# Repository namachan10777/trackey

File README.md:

# Trackey

A splited keyboard that has trackball.

# License
MIT License.

Copyright (c) 2018 Nakano Masaki

## Exception
 * ./pcb/lib/trackey.pretty/MX_ALPS_KH_u1.00.kicad_mod
 * ./pcb/lib/trackey.pretty/D_SOD-123.kicad_mod
 * ./pcb/lib/trackey.pretty/LED_D3.0mm.kicad_mod
 * ./pcb/lib/trackey.pretty/R_Axial.kicad_mod
 * ./pcb/lib/trackey.pretty/SW_Tactile_SPST_Angled.kicad_mod
These footprint's original author is KiCAD.
These are distributed under CC-BY-SA 4.0.

# Third party
## helix
### point of use
 * Key footprint (./pcb/lib/trackey.pretty/MX_ALPS_KH_u1.00.kicad_mod) (modified)
 * Audio Jack footprint (./pcb/lib/trackey.pretty/MJ-4PP-9_rev2.kicad_mod)
### LICENSE
>Copyright (c) 2018 MakotoKurauchi
>
>Permission is hereby granted, free of charge, to any person obtaining a copy
>of this software and associated documentation files (the "Software"), to deal
>in the Software without restriction, including without limitation the rights
>to use, copy, modify, merge, publish, distribute, sublicense, and/or sell
>copies of the Software, and to permit persons to whom the Software is
>furnished to do so, subject to the following conditions:
>
>The above copyright notice and this permission notice shall be included in all
>copies or substantial portions of the Software.
>
>THE SOFTWARE IS PROVIDED "AS IS", WITHOUT WARRANTY OF ANY KIND, EXPRESS OR
>IMPLIED, INCLUDING BUT NOT LIMITED TO THE WARRANTIES OF MERCHANTABILITY,
>FITNESS FOR A PARTICULAR PURPOSE AND NONINFRINGEMENT. IN NO EVENT SHALL THE
>AUTHORS OR COPYRIGHT HOLDERS BE LIABLE FOR ANY CLAIM, DAMAGES OR OTHER
>LIABILITY, WHETHER IN AN ACTION OF CONTRACT, TORT OR OTHERWISE, ARISING FROM,
>OUT OF OR IN CONNECTION WITH THE SOFTWARE OR THE USE OR OTHER DEALINGS IN THE
>SOFTWARE.

## KiCAD Library
### LICENSE
CC-BY-SA 4.0
Copyright (c) KiCAD

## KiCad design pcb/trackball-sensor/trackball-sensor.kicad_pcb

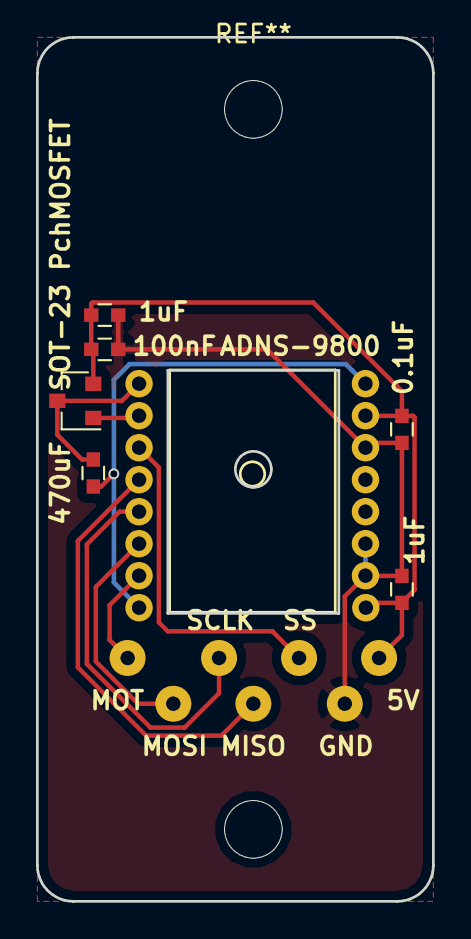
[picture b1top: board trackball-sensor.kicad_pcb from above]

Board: 2 copper layers, 22.0 x 48.0 mm, 14 parts (0 on the bottom side), 10 nets.

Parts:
C1, C4: 1uF; C_0603
C2: 0.1uF; C_0603
C3: 470pF; C_0603
C5: 100nF; C_0603
J1, J2, J3, J4, J5, J6, J7: Conn_01x01; SolderWirePad_single_0-8mmDrill
Q1: Q_PMOS_GDS; SOT-23
U1: ADNS-9800

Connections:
+5V: C1.1, C2.1, C4.2, C5.2, J1.1, Q1.2, U1.9, U1.15
/MISO: J4.1, U1.4
/MOSI: J3.1, U1.6
/MOTION: J6.1, U1.7
/SCLK: J2.1, U1.5
/SS: J5.1, U1.3
GND: C1.2, C2.2, C4.1, C5.1, J7.1, U1.10, U1.11, U1.14
unnamed: C3.1, Q1.3, U1.1
unnamed: C3.2, U1.8, U1.16
unnamed: Q1.1, U1.2

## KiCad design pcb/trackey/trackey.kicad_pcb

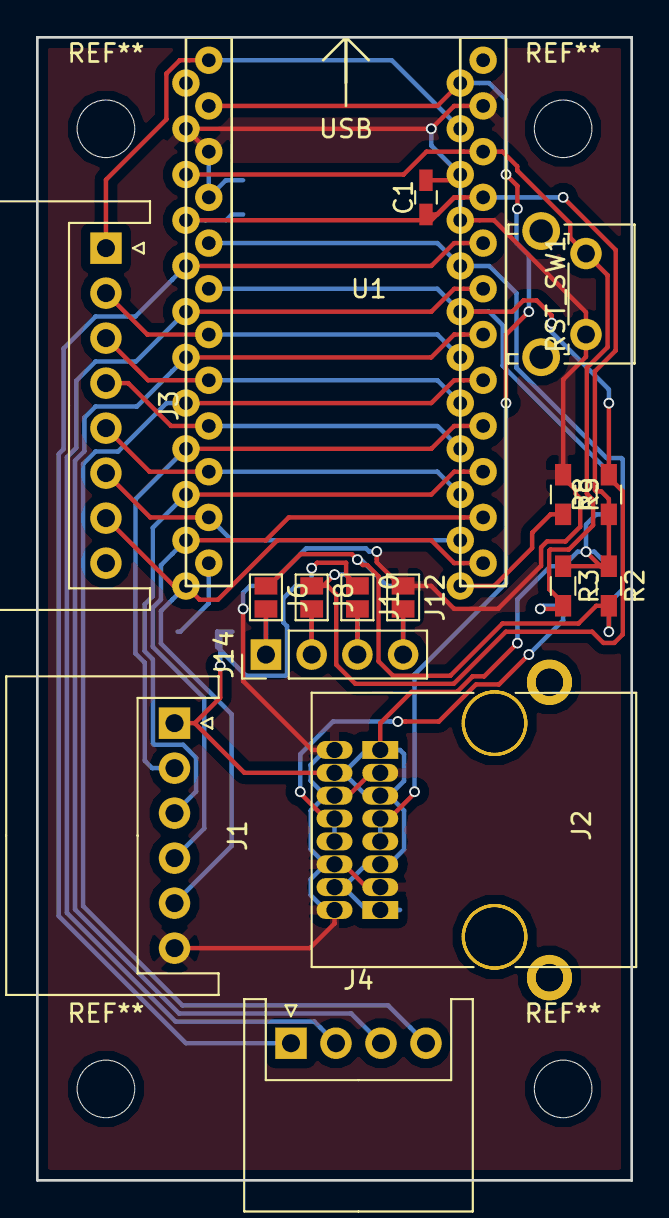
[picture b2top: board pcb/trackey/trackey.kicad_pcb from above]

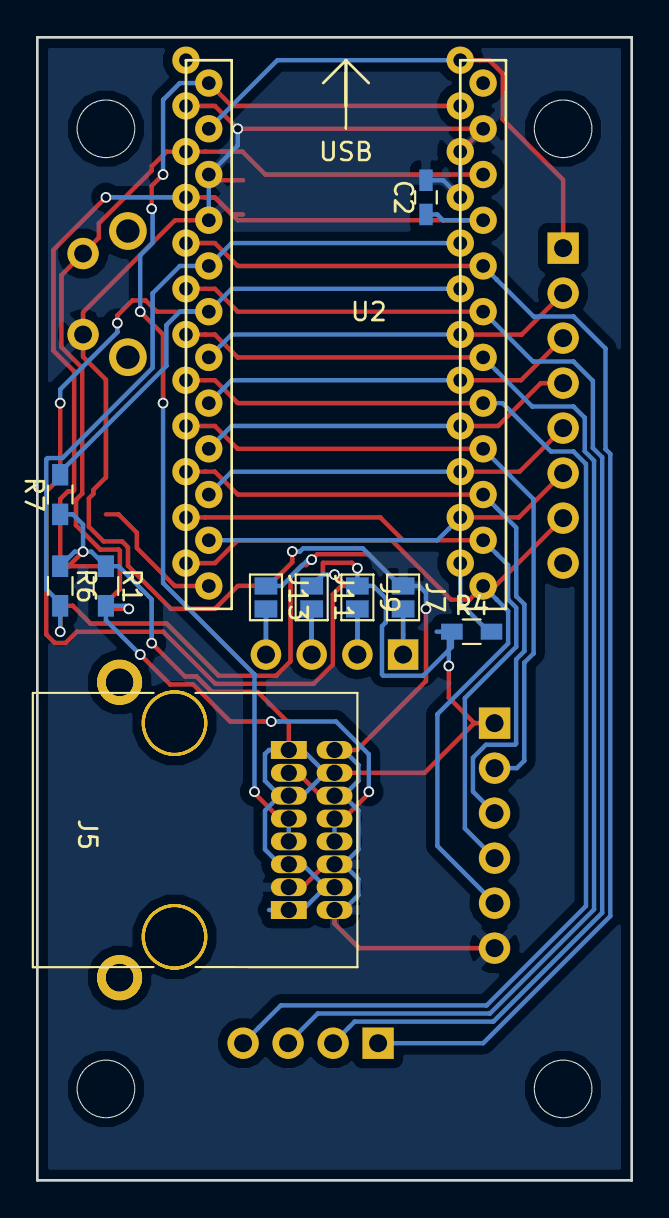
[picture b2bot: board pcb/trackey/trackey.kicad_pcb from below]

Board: 2 copper layers, 33.0 x 63.5 mm, 27 parts (11 on the bottom side), 26 nets.

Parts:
C1, C2: 1uF; C_0603_HandSoldering
J1: trackball_port; JST_XH_S06B-XH-A_06x2.50mm_Angled
J2, J5: RJ45; RJ45_8
J3: COL_port; JST_XH_S08B-XH-A_08x2.50mm_Angled
J4: ROW_port; JST_XH_S04B-XH-A_04x2.50mm_Angled
J6, J8, J10, J12: is_left; GS2
J7, J9, J11, J13: is_right; GS2
J14: OLED_conn; Socket_Strip_Straight_1x04_Pitch2.54mm
R1, R2, R6, R7, R8: R; R_0603_HandSoldering
R3: 2.2kΩ; R_0603_HandSoldering
R4, R5: 2.2k; R_0603_HandSoldering
RST_SW1: SW_DPST_x2; SW_Tactile_SPST_Angled_PTS645Vx39-2LFS
U1, U2: Arduino_Pro_Micro

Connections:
+5V: C1.1, C2.1, J1.1, J2.1, J2.2, J2.3, J5.1, J5.2, J5.3, J9.1, J10.1, R1.1, R2.1, R3.1, R4.1, R6.1, R7.1, R8.1, U1.21, U2.21
/COL0: J3.1, U1.1, U2.2
/COL1: J3.2, U1.7, U2.7
/COL2: J3.3, U1.8, U2.8
/COL3: J3.4, U1.9, U2.9
/COL4: J3.5, U1.10, U2.10
/COL5: J3.6, U1.11, U2.11
/COL6: J1.5, J3.7, U1.13, U2.13
/DATA: J2.5, J5.5, U1.2, U2.1
/MISO: J1.3, U1.15, U2.15
/MOSI: J1.4, U1.14, U2.14
/OLED_1: J6.2, J7.2, J14.1
/OLED_2: J8.2, J9.2, J14.2
/OLED_3: J10.2, J11.2, J14.3
/OLED_4: J12.2, J13.2, J14.4
/ROW0: J4.1, U1.20, U2.20
/ROW1: J4.2, U1.19, U2.19
/ROW2: J4.3, U1.18, U2.18
/ROW3: J4.4, U1.17, U2.17
/RST: J2.4, J5.4, R1.2, R3.2, RST_SW1.1, U1.22, U2.22
/SCL: J8.1, J11.1, R7.2, R8.2, U1.6, U2.6
/SCLK: J1.2, U1.16, U2.16
/SDA: J6.1, J13.1, R2.2, R6.2, U1.5, U2.5
GND: C1.2, C2.2, J1.6, J2.6, J2.7, J2.8, J5.6, J5.7, J5.8, J7.1, J12.1, R5.1, RST_SW1.2, U1.3, U1.4, U1.23, U2.3, U2.4, U2.23
unnamed: R4.2, U1.12
unnamed: R5.2, U2.12

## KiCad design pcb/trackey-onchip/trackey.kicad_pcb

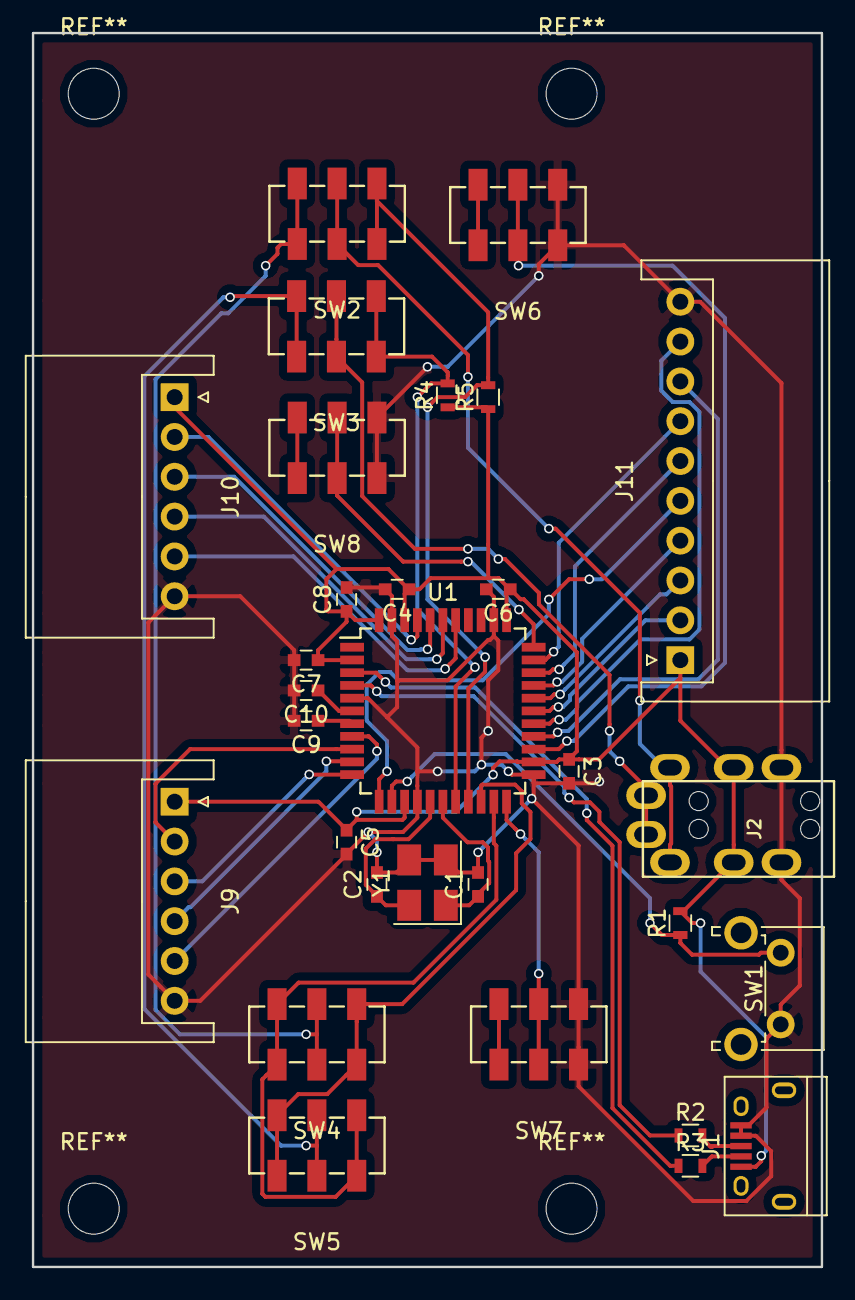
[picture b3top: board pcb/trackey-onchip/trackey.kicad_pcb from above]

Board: 2 copper layers, 49.5 x 77.5 mm, 30 parts (0 on the bottom side), 38 nets.

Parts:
C1, C2: 22pF; C_0603
C3, C4, C5, C6, C7, C8: 0.1uF; C_0603
C9, C10: 1uF; C_0603
J1: USB; USB_Micro-B
J2: Jack; MJ-4PP-9_rev2
J9: Trackball_port; JST_XH_S06B-XH-A_06x2.50mm_Angled
J10: ROW_port; JST_XH_S06B-XH-A_06x2.50mm_Angled
J11: COL_port; JST_XH_S10B-XH-A_10x2.50mm_Angled
R1, R4, R5: 2.2kΩ; R_0603
R2, R3: 22Ω; R_0603
SW1: RST_SW; SW_Tactile_SPST_Angled_PTS645Vx39-2LFS
SW2, SW3, SW8: i2c/RS232; SSSS213202
SW4, SW5: slave/master; SSSS213202
SW6: is_master; SSSS213202
SW7: has_trackball; SSSS213202
U1: ATmega32U4; TQFP-44_10x10mm_Pitch0.8mm
Y1: 16MHz; Crystal_SMD_EuroQuartz_MT-4pin_3.2x2.5mm_HandSoldering

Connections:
+5V: C3.1, C4.1, C5.1, C6.1, C7.1, C8.1, J1.1, J2.3, J9.1, J10.1, J11.1, R1.2, R4.1, R5.1, U1.2, U1.14, U1.24, U1.34, U1.42, U1.44
/COL0: J11.2, U1.28
/COL1: J11.3, U1.29
/COL2: J11.4, U1.30
/COL3: J11.5, U1.12
/COL4: J11.6, U1.31
/COL5: J11.7, U1.32
/COL6: J11.8, U1.26
/COL7: J11.9, U1.27
/D+: R2.1, U1.4
/D-: R3.1, U1.3
/MISO: J9.3, U1.11
/MOSI: J9.4, U1.10
/ROW0: J10.2, U1.41
/ROW1: J10.3, U1.40
/ROW2: J10.4, U1.39
/ROW3: J10.5, U1.38
/RST: R1.1, SW1.1, U1.13
/RX: SW4.3, SW5.1, U1.20
/SCL: R4.2, SW3.3, U1.18
/SCLK: J9.2, U1.9
/SDA: R5.2, SW2.3, U1.19
/TX: SW4.1, SW5.3, U1.21
/Trackball_SS: J9.5, U1.8
GND: C1.2, C2.2, C3.2, C4.2, C5.2, C6.2, C7.2, C8.2, C9.2, C10.2, J1.4, J1.5, J2.4, J9.6, J10.6, J11.10, SW1.2, SW6.3, SW7.3, SW8.3, U1.5, U1.15, U1.23, U1.35, U1.43, Y1.2, Y1.3
unnamed: C1.1, U1.17, Y1.1
unnamed: C2.1, U1.16, Y1.4
unnamed: C9.1, U1.7
unnamed: C10.1, U1.6
unnamed: J1.2, R3.2
unnamed: J1.3, R2.2
unnamed: J2.1, SW3.2
unnamed: J2.2, SW2.2
unnamed: SW2.1, SW4.2
unnamed: SW3.1, SW5.2
unnamed: SW6.2, U1.25
unnamed: SW7.2, U1.22
unnamed: SW8.2, U1.33

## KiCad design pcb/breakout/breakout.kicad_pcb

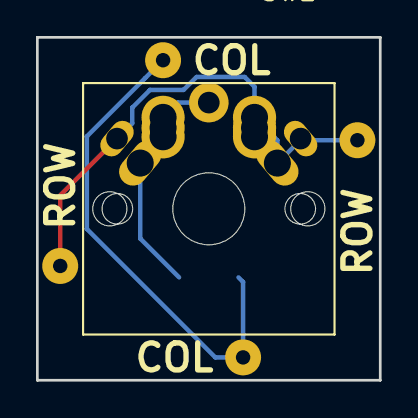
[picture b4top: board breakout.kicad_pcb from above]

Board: 2 copper layers, 19.0 x 19.0 mm, 6 parts (1 on the bottom side), 3 nets.

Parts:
D1: D; D_SOD-123
J1, J2: ROW; SolderWirePad_single_0-8mmDrill
J3, J4: COL; SolderWirePad_single_0-8mmDrill
SW1: SW_DIP_x01; MX_ALPS_KH_u1.00

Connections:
/COL: D1.2, J3.1, J4.1
/ROW: J1.1, J2.1, SW1.1
unnamed: D1.1, SW1.2

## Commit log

2018-04-06 add gitignore
2018-04-06 impl trackball mechanical design
2018-04-06 impl trackball circuit
2018-04-07 fix Arduino Pro Micro
2018-04-07 add footprint library
2018-04-07 fix gitignore
2018-04-07 add main circuit
2018-04-07 complete mechanical design
2018-04-08 add hole to tilt
2018-04-08 fix plate thickness
2018-04-08 add flat model
2018-04-08 fix main pcb active low
2018-04-08 README.md: fix library path
2018-04-08 use standard library's footprint
2018-04-08 RS-232 -> I2C
2018-04-08 add breakout
2018-04-08 ignroe *.net file
2018-04-09 change bearing size 2x3x6 -> 3x3x7
2018-04-09 add cad image to README.md
2018-04-09 sensor pcb: improve silk
2018-04-09 breakout: improve silk
2018-04-09 bend XH
2018-04-09 main pcb:improve circuit layout
2018-04-09 fix mainboard shape
2018-04-09 add main pcb model
2018-04-12 optimize plate
2018-04-13 change cutting side
2018-04-13 add missing files
2018-04-13 cut col0 row3
2018-04-13 reduce thumb penisula
2018-04-14 on-chip schematic
2018-04-15 wiring trackey-onchip
2018-04-15 remove MCP23S17 from trackey.sch
2018-04-18 improve trackey base plate
2018-04-19 improve pcb size
2018-04-19 wiring
2018-04-19 improve trackey pcb
2018-04-19 remove trackey-onchip
2018-04-19 add solid filling to trackball-sensor
